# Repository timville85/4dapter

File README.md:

# 4dapter
### Open Source Controller Adapter for Nintendo Switch / MiSTer / XInput / Batocera / RetroArch

This project combines the NES, SNES, N64 and Genesis DaemonBite Retro Controllers projects together with a custom PCB to support 4 different controllers with a single socketed Arduino Pro Micro. PCB (KiCad + Gerbers), 3D Cases, and muliple firmware versions (Arduino code) all available in this repository.

The controller-reading code (NES/SNES/Genesis/N64 protocol handling) lives once, in
[`lib/4dapterCore`](lib/4dapterCore) (and [`lib/4dapterHID`](lib/4dapterHID) for the HID
output class), shared by every firmware target below — there's no per-variant copy to
keep in sync anymore.

PCB Kits + Fully Assembled units (with firmware of your choice) available on [Tindie](https://www.tindie.com/products/31785/)

Firmware is organized as 3 sketch folders, covering 6 build variants:
* [**4dapter_FW-HID**](4dapter_FW-HID) — Optimized for MiSTer, PC, Raspberry Pi, Batocera, etc. One sketch, 4 selectable layouts (`HID_LAYOUT` build flag): 3 gamepads with NES+SNES combined (default), 3 gamepads with Genesis+N64 combined, 1 combined gamepad (Batocera), or 4 fully separate gamepads.
* [**4dapter_FW-Switch**](4dapter_FW-Switch) — Optimized for Nintendo Switch Online NES, SNES, and Genesis collections - reports as a single wired Switch controller.
* [**4dapter_FW-XInput**](4dapter_FW-XInput) — Optimized for Analogue Pocket Dock - reports as a single wired XInput device.

See each folder's README for build/flash instructions from source, or use the **web
flasher** to flash a pre-built binary straight from your browser — no Arduino IDE, no
board-manager URLs, no manual compiler flags. It works in Chrome or Edge on desktop
(requires [Web Serial](https://developer.chrome.com/docs/capabilities/serial), which
Safari and Firefox don't support).

## Web Flasher

The flasher lives in [`docs/`](docs) as a static site, meant to be hosted with GitHub
Pages directly from this repo:

1. Push a version tag (e.g. `git tag v1.0 && git push origin v1.0`) — this triggers
   [`.github/workflows/build-firmware.yml`](.github/workflows/build-firmware.yml), which
   builds all 6 firmware variants with [`ci/build-all.sh`](ci/build-all.sh) and attaches
   them to a GitHub Release.
2. In the repo's **Settings → Pages**, set the source to **Deploy from a branch**,
   branch `main`, folder `/docs`.
3. The flasher will be live at `https://<your-username>.github.io/4dapter/` and will
   automatically pick up new firmware from each future release.

The flasher fetches the `.hex` file for whichever variant you pick from the latest
GitHub Release and flashes it over the AVR109 ("Caterina") bootloader protocol using
[Web Serial](https://developer.chrome.com/docs/capabilities/serial) — see
[`docs/avr109.js`](docs/avr109.js) for the protocol client. You can also load a `.hex`
file you built yourself instead of using a release.

**MiSTer Users - Important Info:** For maximum compatibly, install the MiSTer controller Map file found in the [MiSTer Maps Folder](https://github.com/timville85/4dapter/tree/main/MiSTer%20Maps) to your `/media/fat/config/inputs` directory on your MiSTer SD card and reboot your MiSTer. After doing this, you'll need to map the N64 controller in the N64 core for all buttons to work. The SNES / Genesis / NES cores will already be properly configured via the Map file.

## Resources and Thanks

**Special thanks to** [Dinierto Designs](https://twitter.com/DiniertoDesigns) **and** [Super Retro City X](https://twitter.com/SuperRetroCity) **for their assistance during development and testing of the 4dapter. Also thanks to** [Mechevarria](https://github.com/mechevarria) **for Batocera support and testing.**

**3D Case files were also designed by** [Dinierto Designs](https://twitter.com/DiniertoDesigns) **and are available in the 3D Cases folder.**

* [DaemonBite Retro Controllers](https://github.com/MickGyver/DaemonBite-Retro-Controllers-USB)
* https://github.com/esden/pretty-kicad-libs
* https://github.com/ddribin/nes-port-breadboard
* https://github.com/Biacco42/ProMicroKiCad
* http://www.neshq.com/hardgen/powerpad.txt
* https://www.instructables.com/Use-an-Arduino-with-an-N64-controller/

See individual README files in firmware folders for more specific instructions on button assignments and firmware configurations.

## Wiring Diagram

Current Draw Readings from DIO Pin 16 (used for 5v supply for DB9 port):
* Krikzz Joyzz:	38mA
* 8BitDo M30 2.4G: 29mA
* OEM SEGA 3-Button Wired: 3mA
* OEM SEGA 6-Button Wired: 3mA
* Retrobit 6-Button Wired: 2mA
(Arduino DIO Max Rated Current: 40mA)

## Tested Controllers

The following controllers have been personally tested and are supported with the Triple Controller. All listed devices also fit when using the 3D Case as well.

NES:
* OEM NES Controller
* OEM NES PowerPad (Default FW Only)
* 8BitDo N30 2.4G Receiver
* 8BitDo NES Retro Receiver

SEGA / Genesis:
* OEM SEGA Master System 2-Button Controller
* OEM Genesis 3-Button Controller
* OEM Genesis 6-Button Controller
* 8BitDo M30 2.4G Receiver
* 8BitDo Genesis Retro Receiver
* Krikzz Joyzz

SNES:
* OEM SNES Controller
* OEM SFC Controller
* OEM SNES NTT Controller (Default FW Only)
* 8BitDo SN30 2.4G Receiver
* 8BitDo SNES Retro Receiver

N64:
* OEM N64 Controller
* Retro Fighters Brawler64 V1/V2
* Retro Fighters Brawler64 Wireless Edition

## 4dapter Bill of Materials (BOM)

4dapter was designed with all components to be through-hole soldered to make the project as accessible as possible.

* **1x 4dapter Main Board**

* **1x 4dapter N64 Daugher Board**

* **1x SNES Socket (90 deg):** [AliExpress - Gamers Zone Store](https://www.aliexpress.com/item/32838396935.html) 

* **1x NES Socket:** [AliExpress - Gamers Zone Store](https://www.aliexpress.com/item/1005003699734963.html)

* **1x Genesis Socket:** [AliExpress - Gamers Zone Store](https://www.aliexpress.com/item/1005003699497865.html)

* **1X N64 Socket:** [AliExpress - Gamers Zone Store](https://www.aliexpress.us/item/3256803534347876.html)

* **1x Arduino Pro Micro (USB-C 3-15V Version):** [AliExpress](https://www.aliexpress.us/item/2251832700923799.html)

* **1x 1x3 90 Degree Male Header:** [Digi-Key](https://www.digikey.com/en/products/detail/sullins-connector-solutions/PREC003SBAN-M71RC/2774931)

* **1x 3.3v Regulator (MCP1700-3302E/TO):** [Digi-Key](https://www.digikey.com/en/products/detail/microchip-technology/MCP1700-3302E-TO/652680)

* **2x 1uF Capacitor:** [Digi-Key](https://www.digikey.com/en/products/detail/tdk-corporation/FG18X5R1H105KRT06/5802871) 

* **1x 6mm x 6mm x 5mm Push Button:** [Digi-Key](https://www.digikey.com/en/products/detail/te-connectivity-alcoswitch-switches/1825910-6/1632536)

* **2x 1x12 Female Header:** [Digi-Key](https://www.digikey.com/en/products/detail/sullins-connector-solutions/PPTC121LFBN-RC/807231)

* **5x M2x10mm Screws for 3D Case**

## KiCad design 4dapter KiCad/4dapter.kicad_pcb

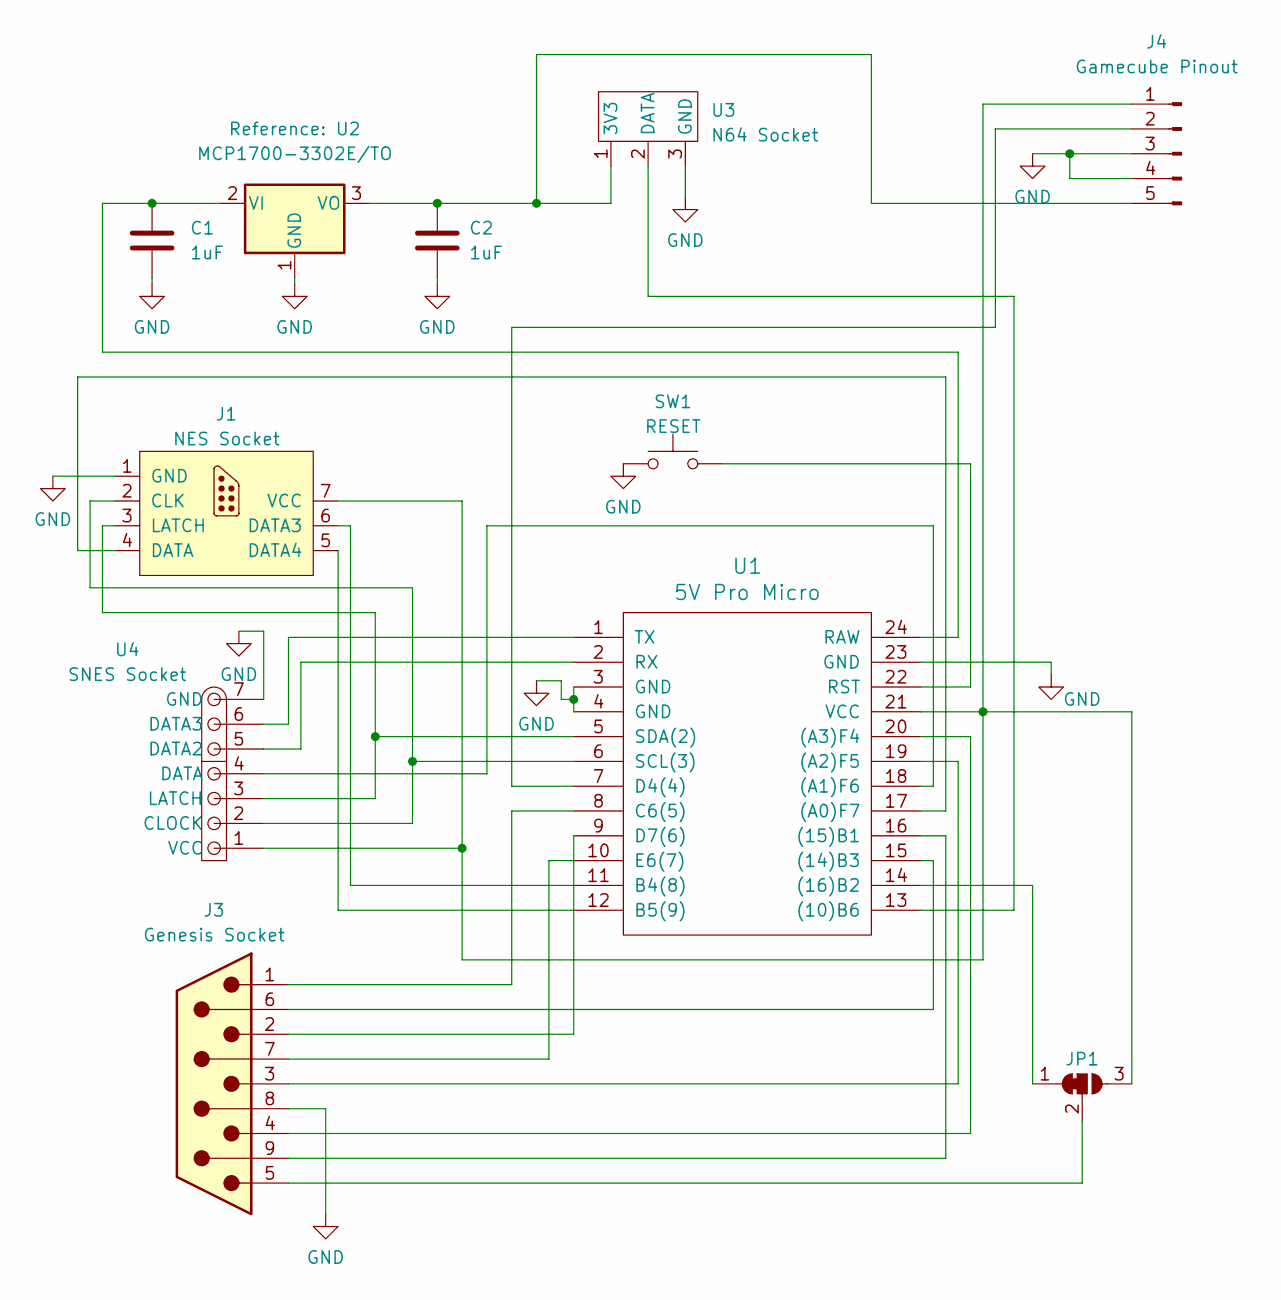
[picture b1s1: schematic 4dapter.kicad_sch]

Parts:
C1, C2: 1uF; C_Rect_L4.0mm_W2.5mm_P2.50mm
J1: NES Socket; NES 90 Socket
J3: Genesis Socket; Genesis 90 Socket
J4: Gamecube Pinout; PinHeader_1x05_P2.54mm_Vertical
JP1: SolderJumper_3_Bridged12; SolderJumper-3_P1.3mm_Bridged12_RoundedPad1.0x1.5mm_NumberL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
SW1: RESET; SW_PUSH_6mm
U1: 5V Pro Micro; Pro Micro Headers
U2: MCP1700-3302E/TO; TO-92_Inline
U3: N64 Socket; N64 Daughter Board
U4: SNES Socket; SNES 90 Socket

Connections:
GND: C1.2, C2.2, J1.1 (GND), J3.8, J4.3, J4.4, SW1.1, U1.3 (GND), U1.4 (GND), U1.23 (GND), U2.1 (GND), U3.3 (GND), U4.7 (GND); also elsewhere on the board
unnamed: J1.2 (CLK), U1.6 (SCL(3)), U4.2 (CLOCK)
unnamed: J1.6 (DATA3), U1.11 (B4(8))
unnamed: J1.5 (DATA4), U1.12 (B5(9))
unnamed: J1.4 (DATA), U1.17 ((A0)F7)
unnamed: J1.3 (LATCH), U1.5 (SDA(2)), U4.3 (LATCH)
unnamed: J1.7 (VCC), J4.1, JP1.3 (B), U1.21 (VCC), U4.1 (VCC)
unnamed: J4.2, U1.7 (D4(4))
unnamed: C2.1, J4.5, U2.3 (VO), U3.1 (3V3)
unnamed: JP1.1 (A), U1.14 ((16)B2)
unnamed: J3.5, JP1.2 (C)
unnamed: U1.13 ((10)B6), U3.2 (DATA)
unnamed: J3.6, U1.15 ((14)B3)
unnamed: J3.9, U1.16 ((15)B1)
unnamed: U1.18 ((A1)F6), U4.4 (DATA)
unnamed: J3.3, U1.19 ((A2)F5)
unnamed: J3.4, U1.20 ((A3)F4)
unnamed: J3.1, U1.8 (C6(5))
unnamed: J3.2, U1.9 (D7(6))
unnamed: J3.7, U1.10 (E6(7))
unnamed: C1.1, U1.24 (RAW), U2.2 (VI)
unnamed 21: SW1.2, U1.22 (RST); also elsewhere on the board
unnamed: U1.2 (RX), U4.5 (DATA2)
unnamed: U1.1 (TX), U4.6 (DATA3)

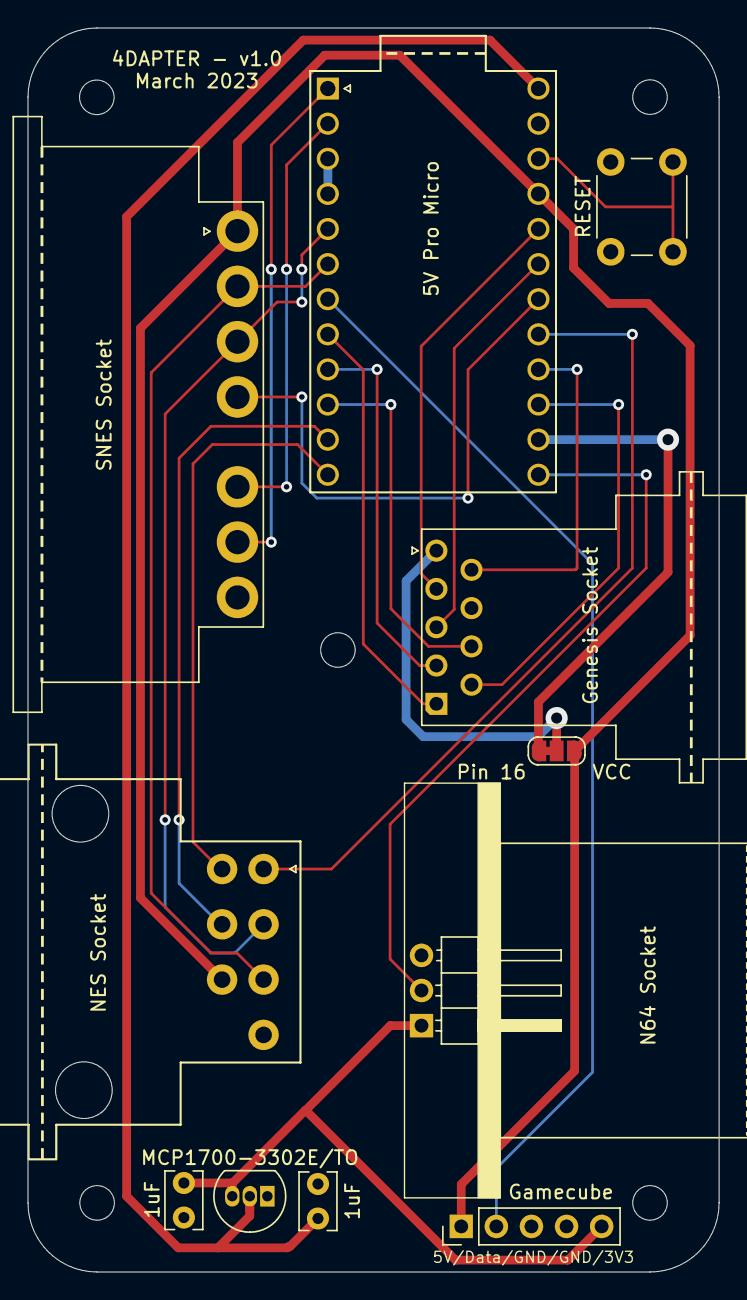
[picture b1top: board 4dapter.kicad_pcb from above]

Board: 2 copper layers, 50.0 x 90.0 mm, 11 parts (0 on the bottom side), 24 nets.

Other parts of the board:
RESET: RESET; SW_PUSH_6mm

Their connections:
GND: RESET.1; also elsewhere on the board
unnamed 21: RESET.2; also elsewhere on the board

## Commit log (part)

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2023-05-15 Added KiCad Projects
2023-05-15 Gerber files added
2023-09-16 Modified N64 value mapping logic
    Modified N64 value mapping logic to set condition to switch between N64 controller raw value and HID 8-bit max (-128 to +127)
2023-09-23 Adjust N64 Select Button Location
2023-10-08 Fix issue with N64 X-axis rolling over incorrectly
2024-05-11 Adjust XInput to use L3/R3 for C-Up / C-Right
2025-01-07 Add HID Alternative Firmware
    Combines Genesis and N64 together, leaving NES and SNES as separate inputs for MiSTer / HID firmware version.
2025-01-08 Update N64 timeouts
    Add support for early Brawler 64 Wireless controllers that have almost 40us delay after the initial query before receiving controller data.
2025-02-22 Added single controller output version of HID Firmware
2025-02-22 Fix bug with N64 "special" button input mapping
2025-02-22 Fix issue with "select" and remove N64 "special"
2025-02-23 Add bool to set N64 C-Stick to individual buttons
2025-02-23 button config for Batocera/Retroarch
2025-02-23 add instructions for Batocera
2025-02-23 updated instructions
2025-02-23 correct typos and remap location
2025-02-23 correct typo
2025-02-23 another typo fix
2025-02-23 fix broken link
2025-02-25 Add alternative config option for Genesis
2025-02-25 setting GEN_MISTER to false
2025-02-25 update instructions
2025-02-26 Update README.md to make defaults clear
2025-02-26 Added thanks to mechevarria for batocera support
2025-03-18 Fix for `select` button as hotkey in Batocera. Update mapping instructions
2025-03-18 image path update
2026-02-14 Adding new 4 HID endpoint variation
2026-02-15 Updated Readme and Comments
